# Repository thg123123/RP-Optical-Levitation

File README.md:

# High-Voltage Op-Amp PCB & Red Pitaya Feedback System

**Role:** Undergraduate Research Assistant | Space-time Optics and Photonics Lab (UCF)

This repository contains the hardware design, fabrication files, and signal manipulation logic for a custom 2-layer high-voltage amplifier PCB and real-time feedback system used in a particle levitation experiment.

## ⚡ Power & Hardware Design Highlights
*   **Voltage Amplification:** Designed an op-amp circuit to step a 1V FPGA signal up to 10V to successfully drive a piezoelectric device.
*   **Power Delivery & Stability:** Integrated bulk capacitors into the PCB layout to stabilize the 15V power supplies during high-frequency operation.
*   **Validation:** Verified a 1 MHz bandwidth using an oscilloscope and validated I/O with signal generators.
*   **Real-Time Feedback:** Implemented quadrant position sensing and low-pass filtering on a Red Pitaya STEMlab 125-14 (Zynq Z-7010).

## 🗂️ Repository Structure

*   **`/OpAMP`**: Contains the complete KiCad project files (`.kicad_pcb`, `.kicad_sch`, `.kicad_pro`) for the 2-layer board.
    *   **`/gerber - OpAMP`**: Complete fabrication packet, including copper layers (`_Cu.gbr`), masks (`_Mask.gbr`), silkscreen, and drill files (`.drl`) ready for manufacturing.
    *   **`/OpAMP LTspice`**: Contains the theoretical circuit simulation files (`Draft3.asc`) and transient analysis data.
*   **`/Test 1 (Signal Manipulation)`**: Contains the low-pass filter logic and signal amplifier testing parameters.

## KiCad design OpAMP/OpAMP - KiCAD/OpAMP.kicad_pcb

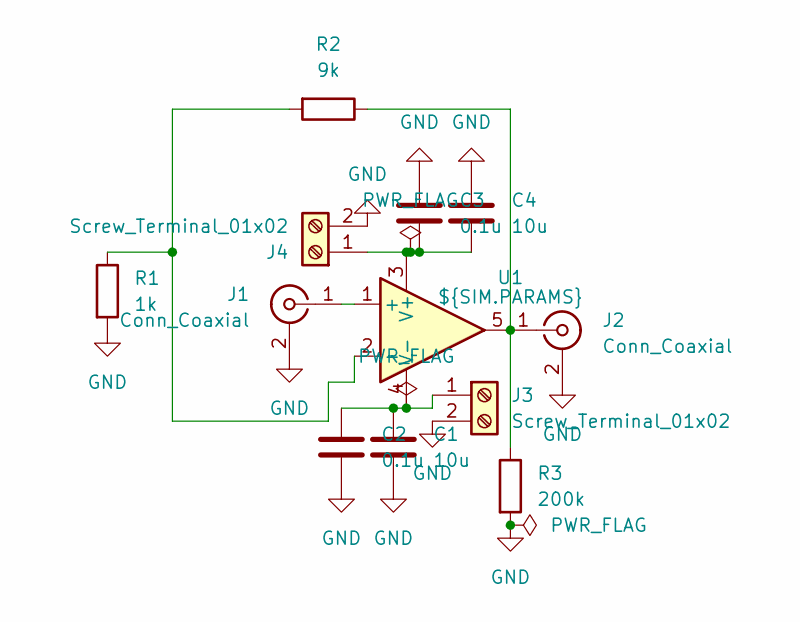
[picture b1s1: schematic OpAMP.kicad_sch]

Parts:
C1, C4: 10u; CP_EIA-3528-21_Kemet-B
C2, C3: 0.1u; C_0805_2012Metric
J1, J2: Conn_Coaxial; SMA_Amphenol_132289_EdgeMount
J3, J4: Screw_Terminal_01x02; TerminalBlock_MaiXu_MX126-5.0-03P_1x03_P5.00mm
R1: 1k; R_0805_2012Metric
R2: 9k; R_0805_2012Metric
R3: 200k; R_0805_2012Metric
U1: ${SIM.PARAMS}; SO-8_3.9x4.9mm_P1.27mm

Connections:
GND: C1.2, C2.2, C3.1, C4.1, J1.2 (Ext), J2.2 (Ext), J3.2, J4.2, R1.2, R3.2
unnamed: J1.1 (In), U1.1 (+)
unnamed: J2.1 (In), R2.1, R3.1, U1.5
unnamed: C1.1, C2.1, J3.1, U1.4 (V-)
unnamed: C3.2, C4.2, J4.1, U1.3 (V+)
unnamed: R1.1, R2.2, U1.2 (-)

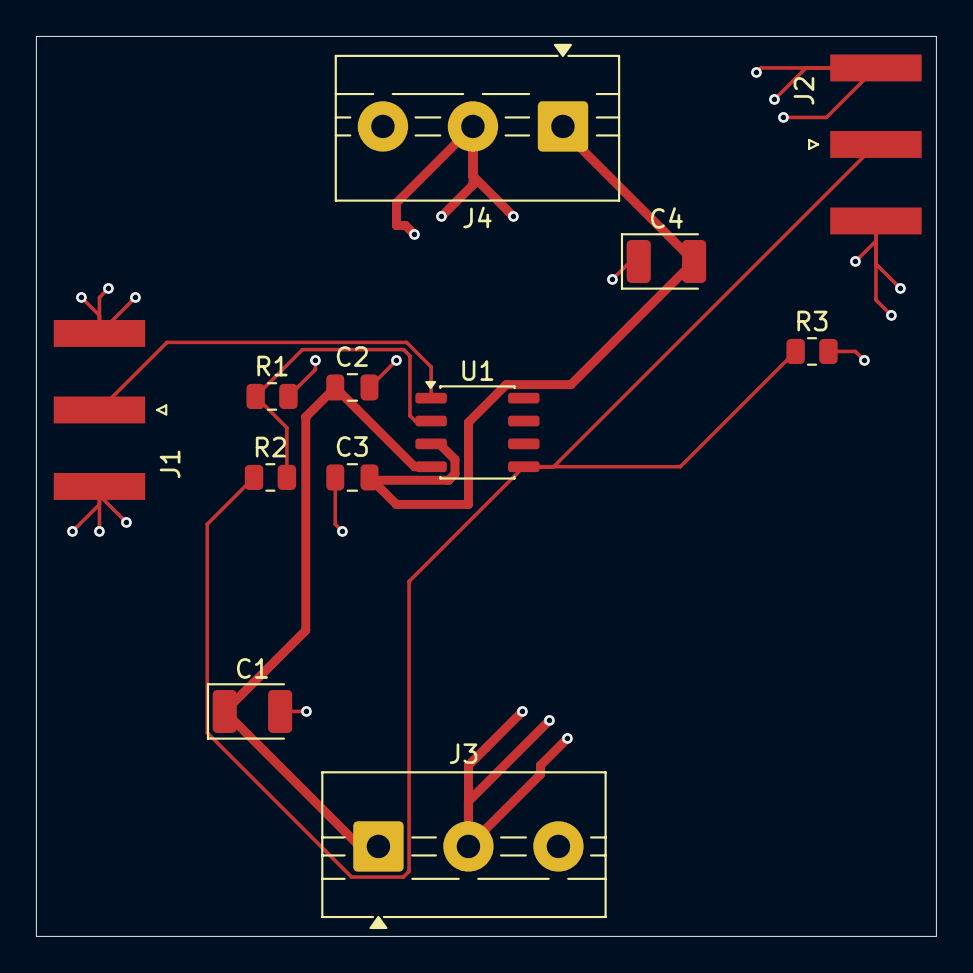
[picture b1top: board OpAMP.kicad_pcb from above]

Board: 2 copper layers, 50.0 x 50.0 mm, 12 parts (0 on the bottom side), 6 nets.

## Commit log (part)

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2025-11-19 Update Signal Manipulation
2025-11-26 Rename Low-Pass Filter to Test 1 (Signal Manipulation)/Low-Pass Filter
2025-11-26 Rename Signal Amplifier to Test 1 (Signal Manipulation)/Signal Amplifier
